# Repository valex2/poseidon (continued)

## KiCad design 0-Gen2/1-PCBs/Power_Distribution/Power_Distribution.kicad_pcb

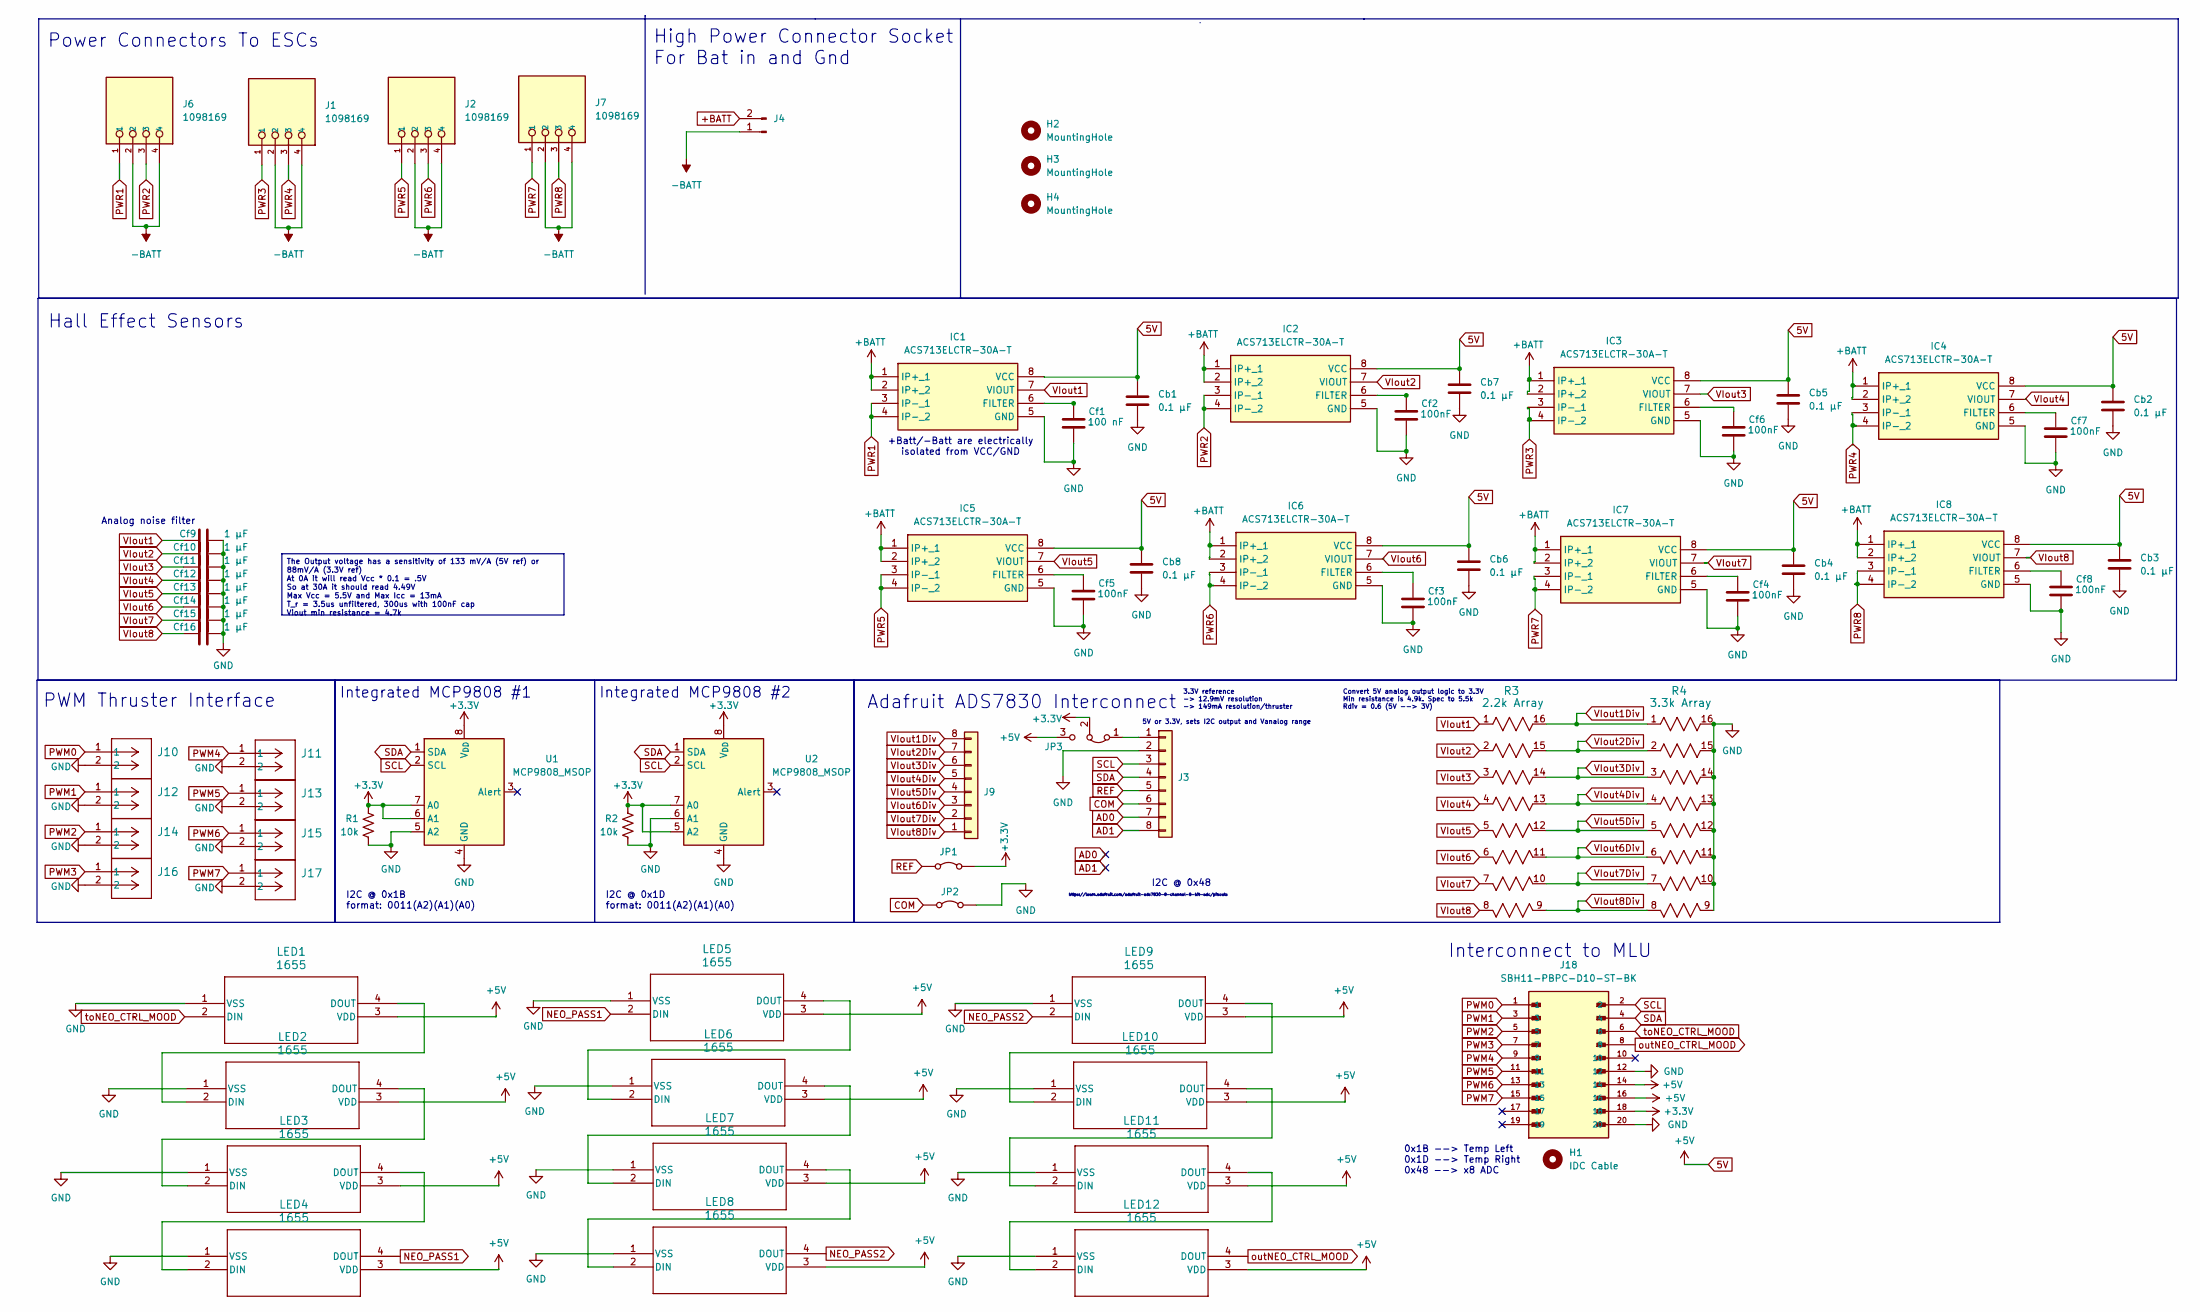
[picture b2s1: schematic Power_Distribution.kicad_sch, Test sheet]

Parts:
Cb1, Cb2, Cb3, Cb4, Cb5, Cb6, Cb7, Cb8: 0.1 µF; C_0805_2012Metric_Pad1.18x1.45mm_HandSolder
Cf1: 100 nF; C_0805_2012Metric_Pad1.18x1.45mm_HandSolder
Cf2, Cf3, Cf4, Cf5, Cf6, Cf7, Cf8: 100nF; C_0805_2012Metric_Pad1.18x1.45mm_HandSolder
Cf9, Cf10, Cf11, Cf12, Cf13, Cf14, Cf15, Cf16: 1 µF; C_0805_2012Metric_Pad1.18x1.45mm_HandSolder
H1: IDC Cable
H2, H3, H4: MountingHole; MountingHole_3.2mm_M3
IC1, IC8: ACS713ELCTR-30A-T; ACS711ELCTR25ABT; Manufacturer_Part_Number ACS713ELCTR-30A-T
IC2, IC3, IC4, IC5, IC6, IC7: ACS713ELCTR-30A-T; MyHalleffectSensor; Manufacturer_Part_Number ACS713ELCTR-30A-T
J1, J2, J6, J7: 1098169; PHOENIX_1098169
J3, J9: Conn_01x08; PinHeader_1x08_P2.54mm_Vertical
J4: Conn_01x02_Pin; AMASS_XT60IPW-M_1x03_P7.20mm_Horizontal
J10, J11, J12, J13, J14, J15, J16, J17: 430450228; CONN_SD-43045-010_02_MOL
J18: SBH11-PBPC-D10-ST-BK; SULLINS_SBH11-PBPC-D10-ST-BK; PARTREV J
JP1, JP2: Jumper_2_Bridged; SolderJumper-2_P1.3mm_Bridged2Bar_RoundedPad1.0x1.5mm
JP3: Jumper_3_Bridged12; SolderJumper-3_P1.3mm_Bridged2Bar12_RoundedPad1.0x1.5mm
LED1, LED2, LED3, LED4, LED5, LED6, LED7, LED8, LED9, LED10, LED11, LED12: 1655; LED_LiteOn_LTST-E563C_PLCC4_5.0x5.0mm_P3.2mm_HandSoldering
R1, R2: 10k; R_0805_2012Metric_Pad1.20x1.40mm_HandSolder
R3: 2.2k Array; 2506_8x_Resistor_Array
R4: 3.3k Array; 2506_8x_Resistor_Array
U1, U2: MCP9808_MSOP; MSOP-8_3x3mm_P0.65mm

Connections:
5V: Cb1.1, Cb2.1, Cb3.1, Cb4.1, Cb5.1, Cb6.1, Cb7.1, Cb8.1, IC1.8 (VCC), IC2.8 (VCC), IC3.8 (VCC), IC4.8 (VCC), IC5.8 (VCC), IC6.8 (VCC), IC7.8 (VCC), IC8.8 (VCC), J18.14, J18.16, JP3.3 (B), LED1.3 (VDD), LED2.3 (VDD), LED3.3 (VDD), LED4.3 (VDD), LED5.3 (VDD), LED6.3 (VDD), LED7.3 (VDD), LED8.3 (VDD), LED9.3 (VDD), LED10.3 (VDD), LED11.3 (VDD), LED12.3 (VDD)
+3.3V: J18.18, JP1.2 (B), JP3.2 (C), R1.1, R2.1, U1.6 (A1), U1.7 (A0), U1.8 (V_{DD}), U2.5 (A2), U2.7 (A0), U2.8 (V_{DD})
+BATT: IC1.1 (IP+_1), IC1.2 (IP+_2), IC2.1 (IP+_1), IC2.2 (IP+_2), IC3.1 (IP+_1), IC3.2 (IP+_2), IC4.1 (IP+_1), IC4.2 (IP+_2), IC5.1 (IP+_1), IC5.2 (IP+_2), IC6.1 (IP+_1), IC6.2 (IP+_2), IC7.1 (IP+_1), IC7.2 (IP+_2), IC8.1 (IP+_1), IC8.2 (IP+_2), J4.2
-BATT: J1.2, J1.4, J2.2, J2.4, J4.1, J6.2, J6.4, J7.2, J7.4
AD0: J3.7
AD1: J3.8
COM: J3.6, JP2.1 (A)
GND: Cb1.2, Cb2.2, Cb3.2, Cb4.2, Cb5.2, Cb6.2, Cb7.2, Cb8.2, Cf1.2, Cf2.2, Cf3.2, Cf4.2, Cf5.2, Cf6.2, Cf7.2, Cf8.2, Cf9.2, Cf10.2, Cf11.2, Cf12.2, Cf13.2, Cf14.2, Cf15.2, Cf16.2, IC1.5 (GND), IC2.5 (GND), IC3.5 (GND), IC4.5 (GND), IC5.5 (GND), IC6.5 (GND), IC7.5 (GND), IC8.5 (GND), J3.2, J10.2, J11.2, J12.2, J13.2, J14.2, J15.2, J16.2, J17.2, J18.12, J18.20, JP2.2 (B), LED1.1 (VSS), LED2.1 (VSS), LED3.1 (VSS), LED4.1 (VSS), LED5.1 (VSS), LED6.1 (VSS), LED7.1 (VSS), LED8.1 (VSS), LED9.1 (VSS), LED10.1 (VSS), LED11.1 (VSS), LED12.1 (VSS), R1.2, R2.2, R4.9, R4.10, R4.11, R4.12, R4.13, R4.14, R4.15, R4.16, U1.4 (GND), U1.5 (A2), U2.4 (GND), U2.6 (A1)
NEO_PASS1: LED4.4 (DOUT), LED5.2 (DIN)
NEO_PASS2: LED8.4 (DOUT), LED9.2 (DIN)
unnamed: Cf1.1, IC1.6 (FILTER)
unnamed: Cf2.1, IC2.6 (FILTER)
unnamed: Cf6.1, IC3.6 (FILTER)
unnamed: Cf7.1, IC4.6 (FILTER)
unnamed: Cf5.1, IC5.6 (FILTER)
unnamed: Cf3.1, IC6.6 (FILTER)
unnamed: Cf4.1, IC7.6 (FILTER)
unnamed: Cf8.1, IC8.6 (FILTER)
unnamed: J3.1, JP3.1 (A)
unnamed: LED1.4 (DOUT), LED2.2 (DIN)
unnamed: LED2.4 (DOUT), LED3.2 (DIN)
unnamed: LED3.4 (DOUT), LED4.2 (DIN)
unnamed: LED5.4 (DOUT), LED6.2 (DIN)
unnamed: LED6.4 (DOUT), LED7.2 (DIN)
unnamed: LED7.4 (DOUT), LED8.2 (DIN)
unnamed: LED9.4 (DOUT), LED10.2 (DIN)
unnamed: LED10.4 (DOUT), LED11.2 (DIN)
unnamed: LED11.4 (DOUT), LED12.2 (DIN)
PWM0: J10.1, J18.1
PWM1: J12.1, J18.3
PWM2: J14.1, J18.5
PWM3: J16.1, J18.7
PWM4: J11.1, J18.9
PWM5: J13.1, J18.11
PWM6: J15.1, J18.13
PWM7: J17.1, J18.15
PWR1: IC1.3 (IP-_1), IC1.4 (IP-_2), J6.1
PWR2: IC2.3 (IP-_1), IC2.4 (IP-_2), J6.3
PWR3: IC3.3 (IP-_1), IC3.4 (IP-_2), J1.1
PWR4: IC4.3 (IP-_1), IC4.4 (IP-_2), J1.3
PWR5: IC5.3 (IP-_1), IC5.4 (IP-_2), J2.1
PWR6: IC6.3 (IP-_1), IC6.4 (IP-_2), J2.3
PWR7: IC7.3 (IP-_1), IC7.4 (IP-_2), J7.1
PWR8: IC8.3 (IP-_1), IC8.4 (IP-_2), J7.3
REF: J3.5, JP1.1 (A)
SCL: J3.3, J18.2, U1.2 (SCL), U2.2 (SCL)
SDA: J3.4, J18.4, U1.1 (SDA), U2.1 (SDA)
VIout1: Cf9.1, IC1.7 (VIOUT), R3.1
VIout1Div: J9.8, R3.16, R4.1
VIout2: Cf10.1, IC2.7 (VIOUT), R3.2
VIout2Div: J9.7, R3.15, R4.2
VIout3: Cf11.1, IC3.7 (VIOUT), R3.3
VIout3Div: J9.6, R3.14, R4.3
VIout4: Cf12.1, IC4.7 (VIOUT), R3.4
VIout4Div: J9.5, R3.13, R4.4
VIout5: Cf13.1, IC5.7 (VIOUT), R3.5
VIout5Div: J9.4, R3.12, R4.5
VIout6: Cf14.1, IC6.7 (VIOUT), R3.6
VIout6Div: J9.3, R3.11, R4.6
VIout7: Cf15.1, IC7.7 (VIOUT), R3.7
VIout7Div: J9.2, R3.10, R4.7
VIout8: Cf16.1, IC8.7 (VIOUT), R3.8
VIout8Div: J9.1, R3.9, R4.8
outNEO_CTRL_MOOD: J18.8, LED12.4 (DOUT)
toNEO_CTRL_MOOD: J18.6, LED1.2 (DIN)

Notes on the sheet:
The Output voltage has a sensitivity of 133 mV/A (5V ref) or 88mV/A (3.3V ref) At 0A it will read Vcc * 0.1 = .5V So at 30A it should read 4.49V Max Vcc = 5.5V and Max Icc = 13mA T_r = 3.5us unfiltered, 300us with 100nF cap Viout min resistance = 4.7k
Interconnect to MLU
Convert 5V analog output logic to 3.3V Min resistance is 4.9k. Spec to 5.5k Rdiv = 0.6 (5V --> 3V)
Analog noise filter
+Batt/-Batt are electrically isolated from VCC/GND
https://learn.adafruit.com/adafruit-ads7830-8-channel-8-bit-adc/pinouts
I2C @ 0x1D format: 0011(A2)(A1)(A0)
I2C @ 0x48
Adafruit ADS7830 Interconnect
5V or 3.3V, sets I2C output and Vanalog range
0x1B --> Temp Left 0x1D --> Temp Right 0x48 --> x8 ADC
High Power Connector Socket For Bat in and Gnd
Integrated MCP9808 #1
Integrated MCP9808 #2
Power Connectors To ESCs
3.3V reference -> 12.9mV resolution -> 149mA resolution/thruster
PWM Thruster Interface
I2C @ 0x1B format: 0011(A2)(A1)(A0)
Hall Effect Sensors

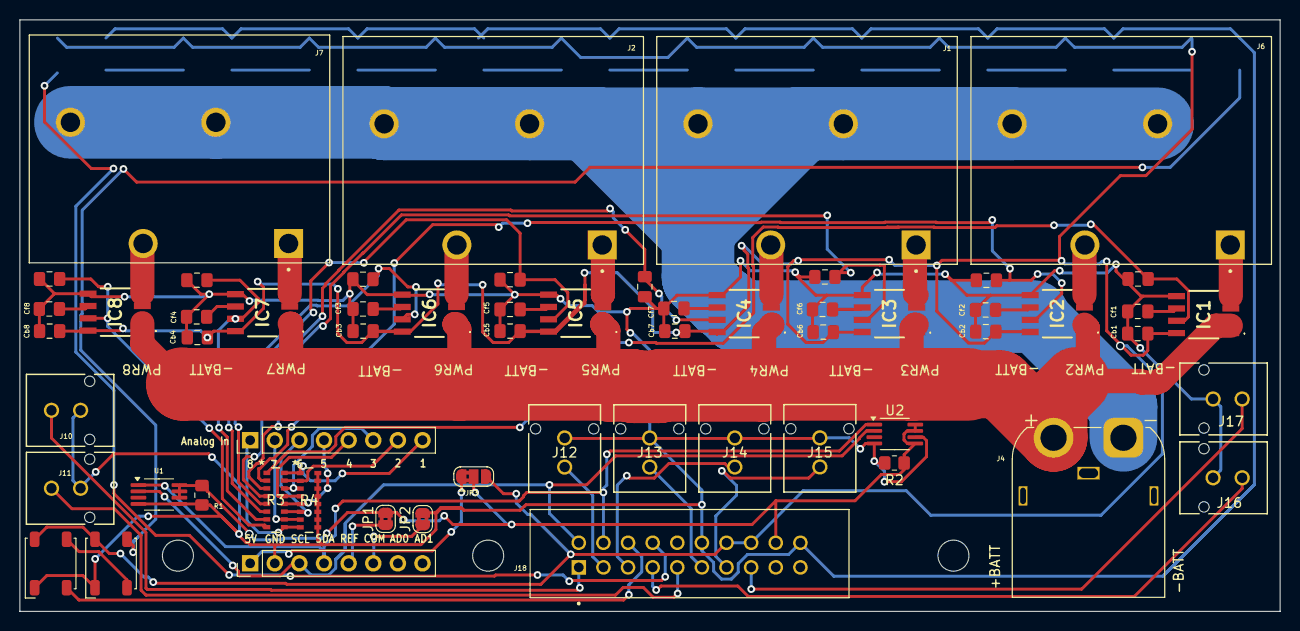
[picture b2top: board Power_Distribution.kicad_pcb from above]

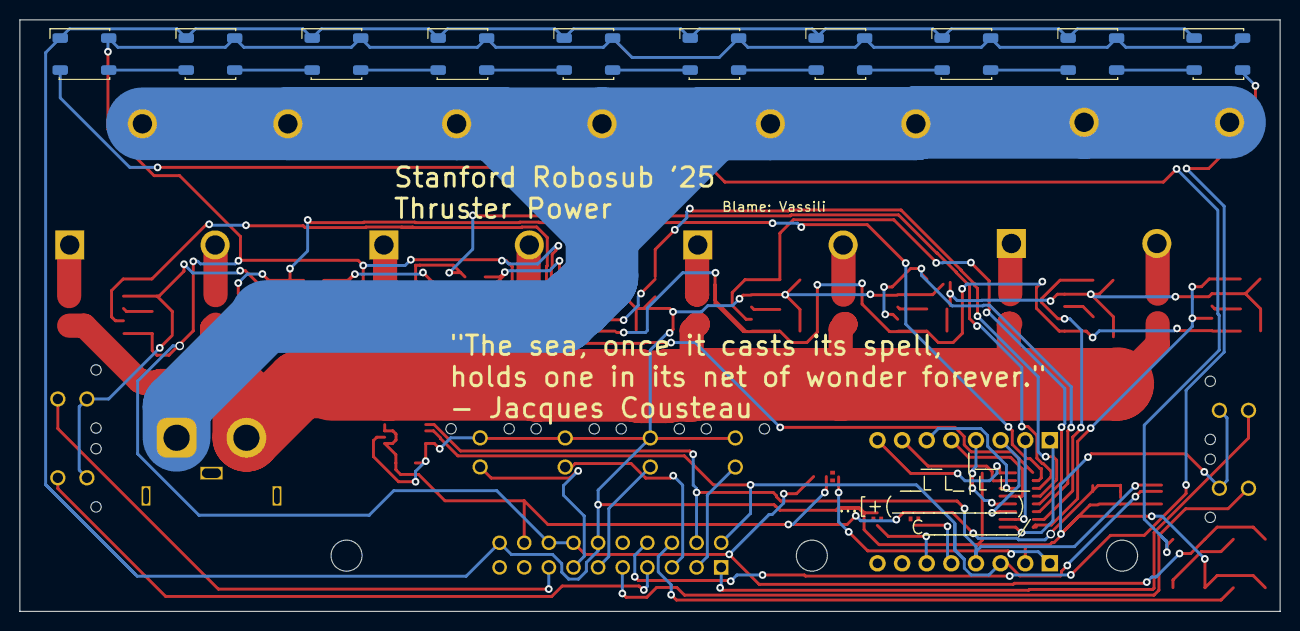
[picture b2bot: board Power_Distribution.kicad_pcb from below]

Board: 2 copper layers, 130.0 x 61.0 mm, 72 parts (10 on the bottom side), 63 nets.

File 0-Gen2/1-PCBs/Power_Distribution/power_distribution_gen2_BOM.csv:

"Reference","Value","Qty","Supplier 1","Supplier 1 S/N"
"Cb1,Cb2,Cb3,Cb4,Cb5,Cb6,Cb7,Cb8,Cf1,Cf2,Cf3,Cf4,Cf5,Cf6,Cf7,Cf8","-- mixed values --","16","https://www.digikey.com/en/products/detail/yageo/CC0805KRX7R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","311-1140-1-ND"
"Cf9,Cf10,Cf11,Cf12,Cf13,Cf14,Cf15,Cf16","1 µF","8","https://www.digikey.com/en/products/detail/samsung-electro-m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","1276-1029-1-ND"
"IC1,IC2,IC3,IC4,IC5,IC6,IC7,IC8","ACS713ELCTR-30A-T","8","https://www.digikey.com/en/products/detail/allegro-microsyst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","620-1193-1-ND"
"J1,J2,J6,J7","1098169","4","https://www.digikey.com/en/products/detail/phoenix-contact/1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","277-1098169-ND"
"J3,J4,J9,JP1,JP2,LED1,LED2,LED3,LED4,LED5,LED6,LED7,LED8,LED9,LED10,LED11,LED12","-- mixed values --","17","",""
"J10,J11,J12,J13,J14,J15,J16,J17","430450228","8","https://www.digikey.com/en/products/detail/molex/0430450228/3310183","WM10659-ND"
"J18","SBH11-PBPC-D10-ST-BK","1","https://www.digikey.com/en/products/detail/sullins-connector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","S9172-ND"
"R1,R2","10k","2","https://www.digikey.com/en/products/detail/panasonic-electro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","P10KACT-ND"
"R3","2.2k Array","1","https://www.digikey.com/en/products/detail/cts-resistor-prod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","60-742C163222JPCT-ND"
"R4","3.3k Array","1","https://www.digikey.com/en/products/detail/cts-resistor-prod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","60-742C163332JPCT-ND"
"U1,U2","MCP9808_MSOP","2","https://www.digikey.com/en/products/detail/microchip-technol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","MCP9808T-E/MSCT-ND"

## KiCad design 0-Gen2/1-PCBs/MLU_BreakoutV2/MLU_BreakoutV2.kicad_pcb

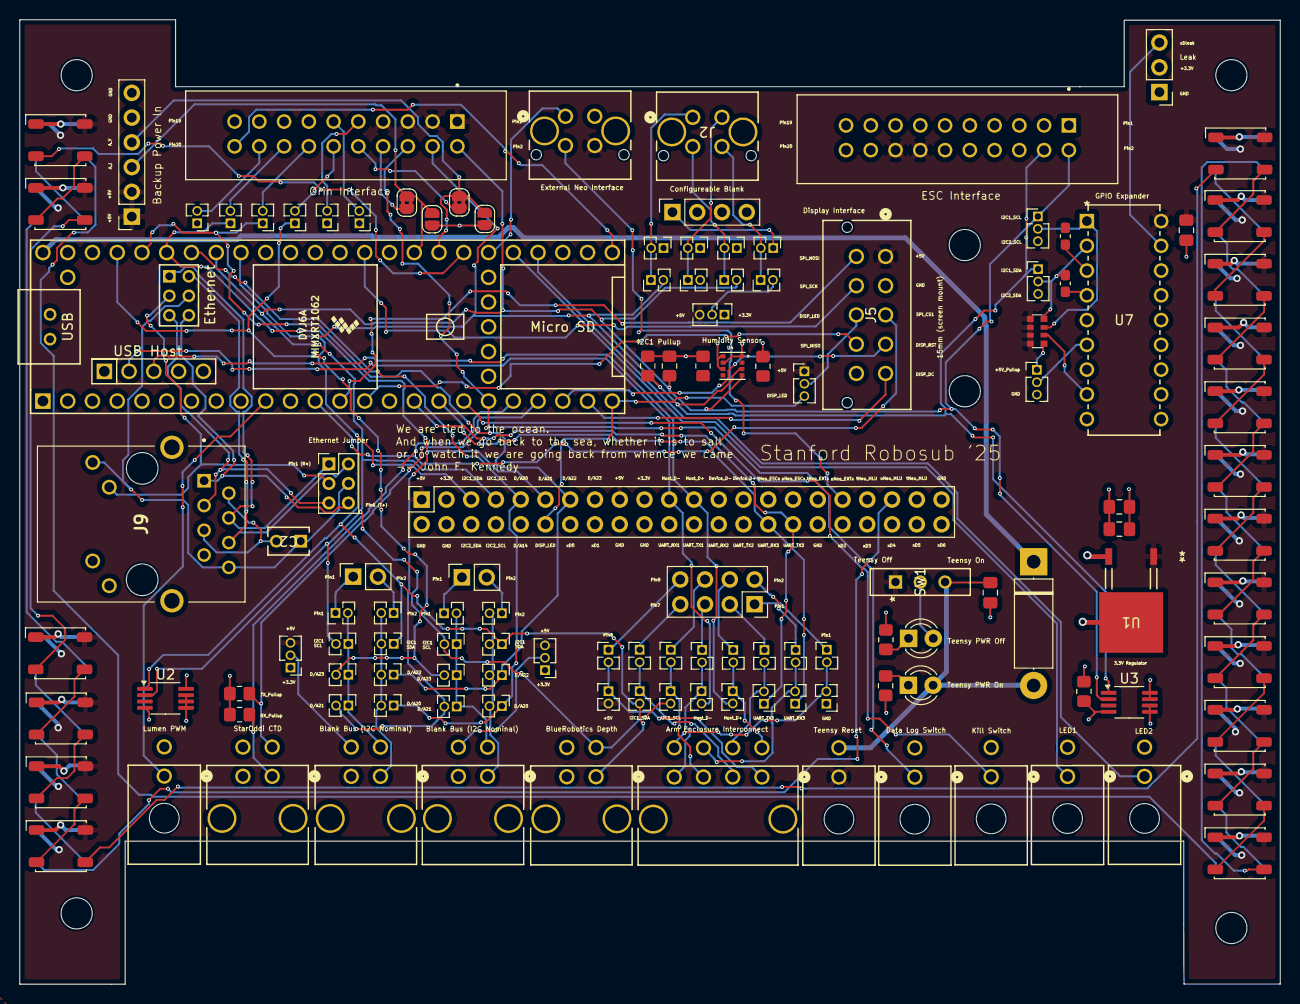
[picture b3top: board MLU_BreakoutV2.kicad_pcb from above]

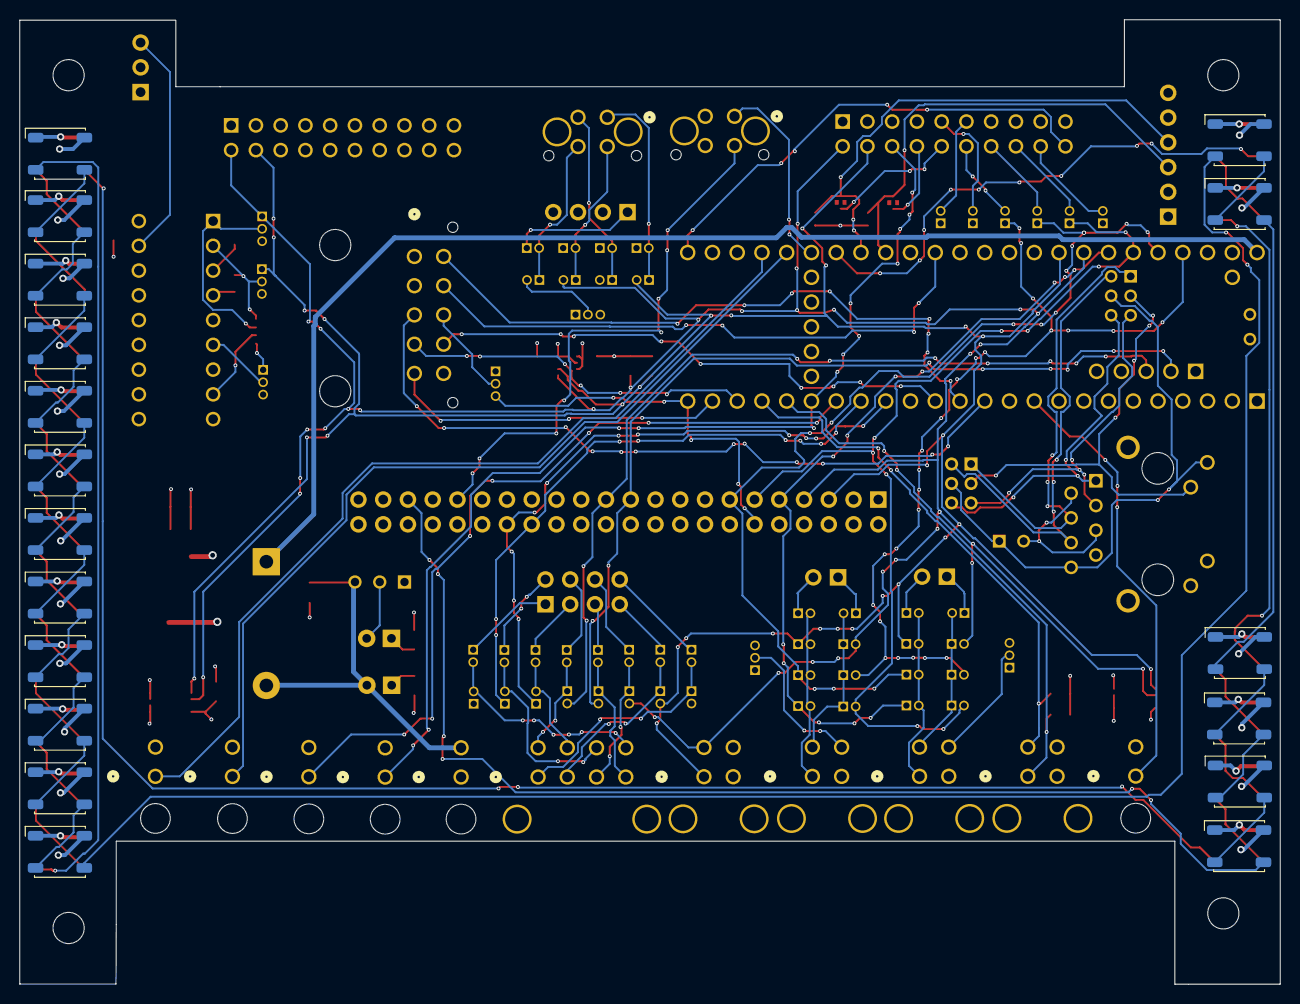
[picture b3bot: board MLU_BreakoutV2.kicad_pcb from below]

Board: 4 copper layers, 129.3 x 99.0 mm, 151 parts (18 on the bottom side), 157 nets.

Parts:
C1, C3, C6: 10uF; C_0805_2012Metric_Pad1.18x1.45mm_HandSolder
C2: 0.1uF; K104K15X7RF5TL2_VIS
C4, C5: 135p; C_0603_1608Metric_Pad1.08x0.95mm_HandSolder
C7: 1uF; C_0805_2012Metric_Pad1.18x1.45mm_HandSolder
D1: 1N5817; D_5W_P12.70mm_Horizontal
D2, D3: LED; LED_D3.0mm
H1, H3, H4, H12: MountingHole; MountingHole_3.2mm_M3
H8, H9: MountingHole_3.2mm_M3
J2, J4: 430450422; CONN_SD-43045-009_04_MOL
J3: Conn_01x03_Pin; PinHeader_1x03_P2.54mm_Vertical
J5: 430451027; CONN_SD-43045-010_10_MOL
J6, J20, J21, J22, J23, J25: 430450228; CONN_SD-43045-001_02_MOL
J7, J13: SBH11-PBPC-D10-ST-BK; SULLINS_SBH11-PBPC-D10-ST-BK
J8: Conn_02x22_Odd_Even; PinSocket_2x22_P2.54mm_Vertical
J9: J1B1211CCD
J10: Conn_02x03_Odd_Even; PinHeader_2x03_P2.00mm_Vertical
J11, J17, J18, J19: 430450422; CONN_SD-43045-008_04_MOL
J12: PixHawk PM02; PinSocket_1x06_P2.54mm_Vertical
J14, J31: Conn_01x02_Socket; PinSocket_1x02_P2.54mm_Vertical
J26: 430450821; CONN_SD-43045-008_08_MOL
J27: PinSocket_2x04_P2.54mm_Vertical
J28: Conn_01x04_Socket; PinSocket_1x04_P2.54mm_Vertical
JP2, JP8, JP9, JP10, JP17, JP40, JP58: Jumper_3_Bridged12; PinHeader_1x03_P1.27mm_Vertical
JP3, JP11, JP12, JP13, JP14, JP15, JP16, JP18, JP19, JP20, JP21, JP22, JP23, JP24, JP25, JP26, JP27, JP28, JP29, JP30, JP31, JP41, JP42, JP43, JP44, JP49, JP50, JP51, JP52, JP53, JP57, JP59, JP60, JP67: Jumper_2_Small_Open; PinHeader_1x02_P1.27mm_Vertical
JP4, JP7: Jumper_2_Small_Open; SolderJumper-2_P1.3mm_Open_RoundedPad1.0x1.5mm
JP5, JP6: Jumper_2_Small_Bridged; SolderJumper-2_P1.3mm_Bridged2Bar_RoundedPad1.0x1.5mm
JP32, JP33, JP34, JP35, JP36, JP37, JP38, JP39, JP45, JP46, JP47, JP48: Jumper_2_Small_Bridged; PinHeader_1x02_P1.27mm_Vertical
LED1, LED2, LED3, LED4, LED5, LED6, LED7, LED8, LED9, LED10, LED11, LED12, LED13, LED14, LED15, LED16, LED17, LED18, LED19, LED20, LED21, LED22, LED23, LED24, LED25, LED26, LED27, LED28, LED29, LED30, LED31, LED32, LED33, LED34, LED35, LED36: 1655; LED_LiteOn_LTST-E563C_PLCC4_5.0x5.0mm_P3.2mm_HandSoldering
R1, R2, R3, R4, R5, R8, R9: 10k; R_0805_2012Metric_Pad1.20x1.40mm_HandSolder
R6, R7: 140; R_0805_2012Metric_Pad1.20x1.40mm_HandSolder
RN1: 10kΩ; R_Array_Convex_4x0612
SW1: 09.03201.02; 09.03201_EAO
U1: BA033CC0FP-E2; TO252-3_ROM
U2, U3: MCP9808_MSOP; MSOP-8_3x3mm_P0.65mm
U4: BME280
U6: Teensy4.1; Teensy41
U7: MCP23008-E_P; MCP3008

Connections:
+3.3V: C6.1, C7.1, J3.2, J7.18, J8.3, J8.19, J17.4, J18.4, J21.2, J25.2, JP2.1 (A), JP17.1 (A), JP58.1 (A), R1.1, R2.1, R3.1, R4.1, R5.1, R8.2, R9.2, U1.3 (OUT), U2.8 (V_{DD}), U3.7 (A0), U3.8 (V_{DD}), U4.6 (VDDIO), U4.8 (VDD)
+5V: C3.1, J4.4, J5.1, J6.1, J7.14, J7.16, J8.1, J8.17, J12.1, J12.2, J13.1, J13.3, J13.5, J13.7, JP2.3 (B), JP17.3 (B), JP34.2 (B), JP40.1 (A), JP58.3 (B), LED1.3 (VDD), LED2.3 (VDD), LED3.3 (VDD), LED4.3 (VDD), LED5.3 (VDD), LED6.3 (VDD), LED7.3 (VDD), LED8.3 (VDD), LED9.3 (VDD), LED10.3 (VDD), LED11.3 (VDD), LED12.3 (VDD), LED13.3 (VDD), LED14.3 (VDD), LED15.3 (VDD), LED16.3 (VDD), LED17.3 (VDD), LED18.3 (VDD), LED19.3 (VDD), LED20.3 (VDD), LED21.3 (VDD), LED22.3 (VDD), LED23.3 (VDD), LED24.3 (VDD), LED25.3 (VDD), LED26.3 (VDD), LED27.3 (VDD), LED28.3 (VDD), LED29.3 (VDD), LED30.3 (VDD), LED31.3 (VDD), LED32.3 (VDD), LED33.3 (VDD), LED34.3 (VDD), LED35.3 (VDD), LED36.3 (VDD), RN1.5 (R4.2), RN1.6 (R3.2), RN1.7 (R2.2), RN1.8 (R1.2), SW1.1, U1.1 (Vcc), U7.18 (VDD)
Analog_Current: J12.3, JP4.1 (A), JP5.2 (B), U6.33 (41_A17)
Analog_Voltage: J12.4, JP6.2 (B), JP7.2 (B), U6.32 (40_A16)
DISP_DC: J5.5, U6.23 (31_CTX3)
DISP_LED: J8.12, JP40.3 (B), U6.24 (32_OUT1B)
DISP_RST: J5.4, U6.22 (30_CRX3)
Device_D+: J8.27, JP41.1 (A), U6.67 (D+)
Device_D-: J8.25, JP49.1 (A), U6.66 (D-)
Dled1: J22.1, U6.29 (37_CS)
Dled2: J23.1, U6.28 (36_CS)
Dswitch1: J21.1, U6.18 (26_A12_MOSI1)
Dswitch2: J13.6, J25.1, U6.19 (27_A13_SCK1)
D/A14: J8.10, U6.36 (14_A0_TX3_SPDIF_OUT)
D/A20: J8.9, JP16.1 (A), JP19.1 (A), JP53.1 (A), U6.42 (20_A6_TX5_LRCLK1)
D/A21: J8.11, JP24.2 (B), JP52.1 (A), JP60.2 (B), U6.43 (21_A7_RX5_BCLK1)
D/A22: J8.13, JP15.1 (A), JP20.1 (A), JP51.1 (A), U6.44 (22_A8_CTX1)
D/A23: J8.15, JP50.1 (A), JP57.2 (B), JP59.2 (B), U6.45 (23_A9_CRX1_MCLK1)
ETH_GND: C2.1, J9.8 (GND), J9.9, J10.4, U6.64 (GND)
GND: C1.2, C3.2, C4.2, C5.2, C6.2, C7.2, J3.1, J4.2, J5.2, J7.12, J7.20, J8.2, J8.4, J8.18, J8.20, J8.34, J8.43, J11.2, J12.5, J12.6, J13.13, J13.15, J13.17, J13.19, J17.2, J18.2, J19.2, J20.2, J22.2, J23.2, JP4.2 (B), JP7.1 (A), JP10.3 (B), JP38.1 (A), JP46.2 (B), LED1.1 (VSS), LED2.1 (VSS), LED3.1 (VSS), LED4.1 (VSS), LED5.1 (VSS), LED6.1 (VSS), LED7.1 (VSS), LED8.1 (VSS), LED9.1 (VSS), LED10.1 (VSS), LED11.1 (VSS), LED12.1 (VSS), LED13.1 (VSS), LED14.1 (VSS), LED15.1 (VSS), LED16.1 (VSS), LED17.1 (VSS), LED18.1 (VSS), LED19.1 (VSS), LED20.1 (VSS), LED21.1 (VSS), LED22.1 (VSS), LED23.1 (VSS), LED24.1 (VSS), LED25.1 (VSS), LED26.1 (VSS), LED27.1 (VSS), LED28.1 (VSS), LED29.1 (VSS), LED30.1 (VSS), LED31.1 (VSS), LED32.1 (VSS), LED33.1 (VSS), LED34.1 (VSS), LED35.1 (VSS), LED36.1 (VSS), R3.2, R6.2, R7.2, U1.2 (GND), U2.4 (GND), U2.5 (A2), U2.6 (A1), U2.7 (A0), U3.4 (GND), U3.5 (A2), U3.6 (A1), U4.1 (GND), U4.7 (GND), U6.1 (GND), U6.34 (GND), U6.47 (GND), U7.3 (A2), U7.4 (A1), U7.5 (A0), U7.9 (VSS)
GPIOExp_INT: RN1.2 (R2.1), U6.37 (15_A1_RX3_SPDIF_IN), U7.8 (INT)
Host_D+: J8.23, JP39.2 (B), U6.57 (D+)
Host_D-: J8.21, JP37.2 (B), U6.56 (D-)
I2C1_SCL: J7.2, J8.7, J13.2, J17.3, JP8.1 (A), JP11.2 (B), JP23.2 (B), JP36.2 (B), JP47.2 (B), R5.2, U2.2 (SCL), U3.2 (SCL), U4.4 (SCK), U6.41 (19_A5_SCL)
I2C1_SDA: J7.4, J8.5, J13.4, J17.1, JP9.1 (A), JP14.1 (A), JP18.1 (A), JP35.2 (B), JP45.2 (B), R4.2, U2.1 (SDA), U3.1 (SDA), U4.3 (SDI), U6.40 (18_A4_SDA)
I2C2_SCL: J8.8, JP8.3 (B), U6.38 (16_A2_RX4_SCL1)
I2C2_SDA: J8.6, JP9.3 (B), U6.39 (17_A3_TX4_SDA1)
LED: J9.10, J10.3, U6.61 (LED)
Lumen_PWM: J20.1, U6.10 (8_TX2_IN1)
NEO_PASS1: LED4.4 (DOUT), LED5.2 (DIN)
NEO_PASS2: LED8.4 (DOUT), LED9.2 (DIN)
NEO_PASS3: LED12.4 (DOUT), LED13.2 (DIN)
NEO_PASS4: LED16.4 (DOUT), LED17.2 (DIN)
NEO_PASS5: LED20.4 (DOUT), LED21.2 (DIN)
NEO_PASS6: LED24.4 (DOUT), LED25.2 (DIN)
NEO_PASS7: LED28.4 (DOUT), LED29.2 (DIN)
NEO_PASS8: LED32.4 (DOUT), LED33.2 (DIN)
unnamed: C2.2, J9.2, J9.5
unnamed: C1.1, D1.2 (A), D3.2 (A), J6.2, SW1.3
unnamed: D2.2 (A), SW1.2
unnamed: D2.1 (K), R6.1
unnamed: D3.1 (K), R7.1
unnamed: J14.1, JP22.1 (A)
unnamed: J14.2, JP21.1 (A)
unnamed: J27.1, JP31.1 (A)
unnamed: J27.2, JP30.1 (A)
unnamed: J27.3, JP29.1 (A)
unnamed: J27.4, JP28.1 (A)
unnamed: J27.5, JP27.1 (A)
unnamed: J27.6, JP26.1 (A)
unnamed: J27.7, JP25.1 (A)
unnamed: J27.8, JP3.1 (A)
unnamed: J28.1, JP44.1 (A)
unnamed: J28.2, JP43.1 (A)
unnamed: J28.3, JP42.1 (A)
unnamed: J28.4, JP67.1 (A)
unnamed: J31.1, JP12.1 (A)
unnamed: J31.2, JP13.1 (A)
unnamed: JP2.2 (C), JP48.2 (B)
unnamed: J26.1, JP3.2 (B), JP34.1 (A)
unnamed: J13.8, JP5.1 (A)
unnamed: J13.10, JP6.1 (A)
unnamed: C4.1, JP8.2 (C), RN1.3 (R3.1), U7.1 (SCL)
unnamed: C5.1, JP9.2 (C), RN1.4 (R4.1), U7.2 (SDA)
unnamed: JP10.1 (A), RN1.1 (R1.1)
unnamed: JP10.2 (C), U7.6 (*RESET)
unnamed: J19.3, JP11.1 (A), JP12.2 (B), JP59.1 (A), JP60.1 (A)
unnamed: J19.1, JP13.2 (B), JP14.2 (B), JP15.2 (B), JP16.2 (B)
unnamed: J19.4, JP17.2 (C)
unnamed: J11.1, JP18.2 (B), JP19.2 (B), JP20.2 (B), JP21.2 (B)
unnamed: J11.3, JP22.2 (B), JP23.1 (A), JP24.1 (A), JP57.1 (A)
unnamed: J26.2, JP25.2 (B), JP35.1 (A)
unnamed: J26.3, JP26.2 (B), JP36.1 (A)
unnamed: J26.4, JP27.2 (B), JP37.1 (A)
unnamed: J26.5, JP28.2 (B), JP39.1 (A)
unnamed: J26.6, JP29.2 (B), JP33.2 (B)
unnamed: J26.7, JP30.2 (B), JP32.2 (B)
unnamed: J26.8, JP31.2 (B), JP38.2 (B)
unnamed: J5.8, JP40.2 (C)
unnamed: J13.11, JP41.2 (B)
unnamed: J2.2, JP42.2 (B), JP46.1 (A)
unnamed: J2.3, JP43.2 (B), JP47.1 (A)
unnamed: J2.4, JP44.2 (B), JP48.1 (A)
unnamed: J2.1, JP45.1 (A), JP67.2 (B)
unnamed: J13.9, JP49.2 (B)
unnamed: J13.12, JP50.2 (B)
unnamed: J13.14, JP51.2 (B)
unnamed: J13.16, JP52.2 (B)
unnamed: J13.18, JP53.2 (B)
unnamed: J11.4, JP58.2 (C)
unnamed: LED1.4 (DOUT), LED2.2 (DIN)
unnamed: LED2.4 (DOUT), LED3.2 (DIN)
unnamed: LED3.4 (DOUT), LED4.2 (DIN)
unnamed: LED5.4 (DOUT), LED6.2 (DIN)
unnamed: LED6.4 (DOUT), LED7.2 (DIN)
unnamed: LED7.4 (DOUT), LED8.2 (DIN)
unnamed: LED9.4 (DOUT), LED10.2 (DIN)
unnamed: LED10.4 (DOUT), LED11.2 (DIN)
unnamed: LED11.4 (DOUT), LED12.2 (DIN)
unnamed: LED13.4 (DOUT), LED14.2 (DIN)
unnamed: LED14.4 (DOUT), LED15.2 (DIN)
unnamed: LED15.4 (DOUT), LED16.2 (DIN)
unnamed: LED17.4 (DOUT), LED18.2 (DIN)
unnamed: LED18.4 (DOUT), LED19.2 (DIN)
unnamed: LED19.4 (DOUT), LED20.2 (DIN)
unnamed: LED21.4 (DOUT), LED22.2 (DIN)
unnamed: LED22.4 (DOUT), LED23.2 (DIN)
unnamed: LED23.4 (DOUT), LED24.2 (DIN)
unnamed: LED25.4 (DOUT), LED26.2 (DIN)
unnamed: LED26.4 (DOUT), LED27.2 (DIN)
unnamed: LED27.4 (DOUT), LED28.2 (DIN)
unnamed: LED29.4 (DOUT), LED30.2 (DIN)
unnamed: LED30.4 (DOUT), LED31.2 (DIN)
unnamed: LED31.4 (DOUT), LED32.2 (DIN)
unnamed: LED33.4 (DOUT), LED34.2 (DIN)
unnamed: LED34.4 (DOUT), LED35.2 (DIN)
unnamed: LED35.4 (DOUT), LED36.2 (DIN)
unnamed: R2.2, U4.2 (CSB)
unnamed: R1.2, U4.5 (SDO)
PWM0: J7.1, U6.2 (0_RX1_CRX2_CS1)
PWM1: J7.3, U6.3 (1_TX1_CTX2_MISO1)
PWM2: J7.5, U6.4 (2_OUT2)
PWM3: J7.7, U6.5 (3_LRCLK2)
PWM4: J7.9, U6.6 (4_BCLK2)
PWM5: J7.11, U6.7 (5_IN2)
PWM6: J7.13, U6.8 (6_OUT1D)
PWM7: J7.15, U6.9 (7_RX2_OUT1A)
R+: J9.4, J10.1, U6.60 (R+)
R-: J9.6, J10.2, U6.65 (R-)
SPI_CS1: J5.3, U6.12 (10_CS_MQSR)
SPI_MISO: J5.9, U6.14 (12_MISO_MQSL)
SPI_MOSI: J5.6, U6.13 (11_MOSI_CTX1)
SPI_SCK: J5.7, U6.35 (13_SCK_LED)
T+: J9.1, J10.6, U6.63 (T+)
T-: J9.3, J10.5, U6.62 (T-)
Teensy_5V: D1.1 (K), U6.48 (VIN)
UART_RX1: J8.24, U6.26 (34_RX8)
UART_RX2: J8.26, J18.1, R9.1, U6.20 (28_RX7)
UART_RX3: J8.30, JP32.1 (A), U6.17 (25_A11_RX6_SDA2)
UART_TX1: J8.22, U6.27 (35_TX8)
UART_TX2: J8.28, J18.3, R8.1, U6.21 (29_TX7)
UART_TX3: J8.32, JP33.1 (A), U6.16 (24_A10_TX6_SCL2)
outNEO_CTRL_ESCs: J7.8, J8.31
outNEO_CTRL_EXTs: J4.3, J8.35
outNEO_CTRL_MLU: J8.39, LED36.4 (DOUT)
toNEO_CTRL_ESCs: J7.6, J8.29, U6.11 (9_OUT1C)
toNEO_CTRL_EXTs: J4.1, J8.33, U6.30 (38_CS1_IN1)
toNEO_CTRL_MLU: J8.37, LED1.2 (DIN), U6.31 (39_MISO1_OUT1A)
toNEO_CTRL_Orin: J8.41, J13.20, U6.25 (33_MCLK2)
xD0: J8.14, U7.10 (GP0)
xD1: J8.16, U7.11 (GP1)
xD2: J8.36, U7.12 (GP2)
xD3: J8.38, U7.13 (GP3)
xD4: J8.40, U7.14 (GP4)
xD5: J8.42, U7.15 (GP5)
xD6: J8.44, U7.16 (GP6)
xDleak: J3.3, U7.17 (GP7)

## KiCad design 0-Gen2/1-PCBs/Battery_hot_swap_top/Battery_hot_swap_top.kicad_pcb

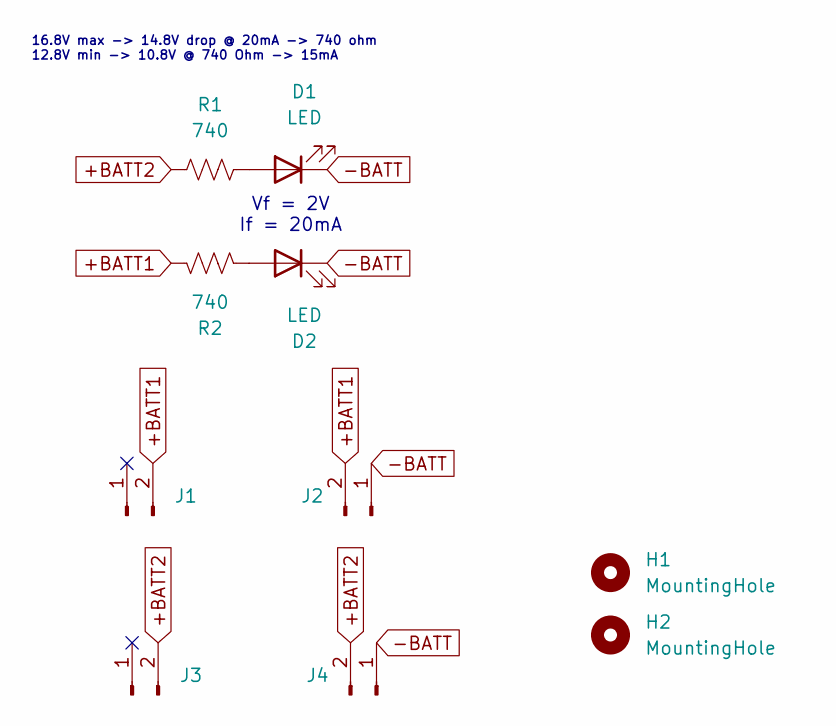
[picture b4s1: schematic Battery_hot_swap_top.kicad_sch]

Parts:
D1, D2: LED; LED_D4.0mm
H1, H2: MountingHole; MountingHole_3.2mm_M3
J1, J3: Conn_01x02_Pin; AMASS_XT60-M_1x02_P7.20mm_Vertical
J2, J4: Conn_01x02_Pin; AMASS_XT60-F_1x02_P7.20mm_Vertical
R1, R2: 740; R_0805_2012Metric_Pad1.20x1.40mm_HandSolder

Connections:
+BATT1: J1.2, J2.2, R2.1
+BATT2: J3.2, J4.2, R1.1
-BATT: D1.1 (K), D2.1 (K), J2.1, J4.1
unnamed: D1.2 (A), R1.2
unnamed: D2.2 (A), R2.2

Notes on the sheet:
16.8V max -> 14.8V drop @ 20mA -> 740 ohm 12.8V min -> 10.8V @ 740 Ohm -> 15mA
Vf = 2V If = 20mA

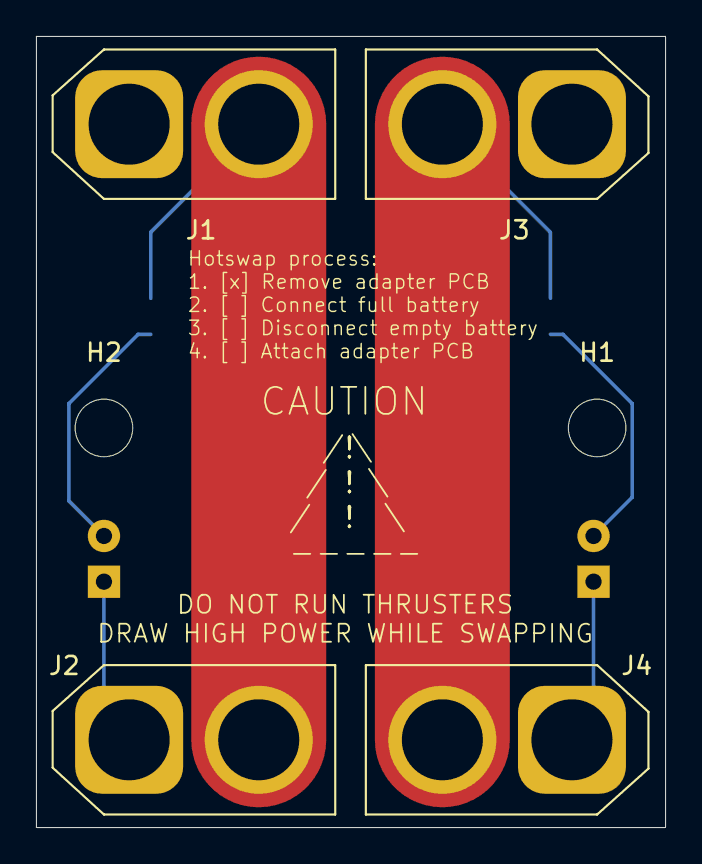
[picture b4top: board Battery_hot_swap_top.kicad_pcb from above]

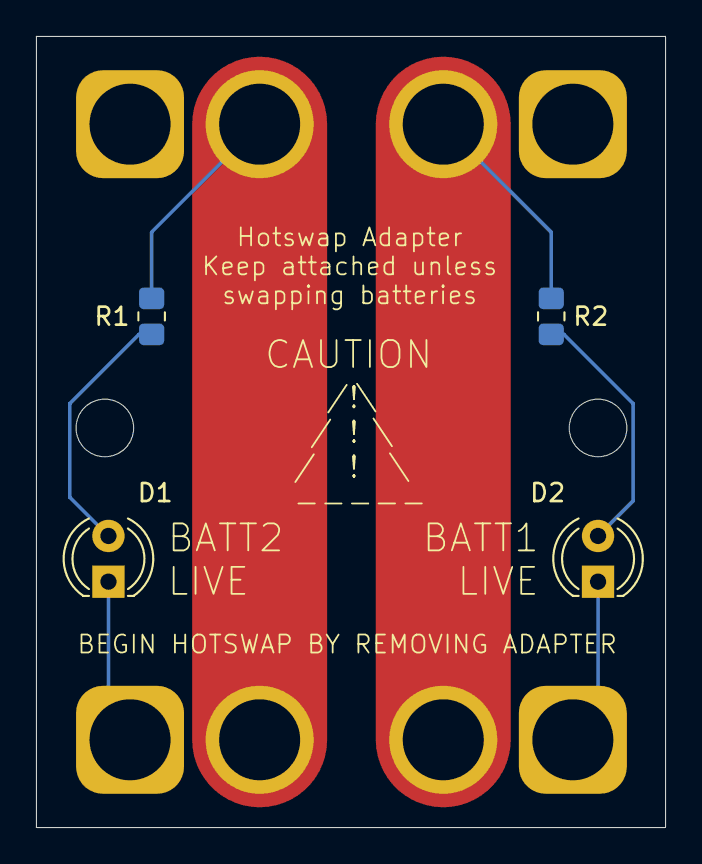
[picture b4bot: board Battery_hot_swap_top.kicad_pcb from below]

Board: 2 copper layers, 34.9 x 43.9 mm, 10 parts (4 on the bottom side), 5 nets.

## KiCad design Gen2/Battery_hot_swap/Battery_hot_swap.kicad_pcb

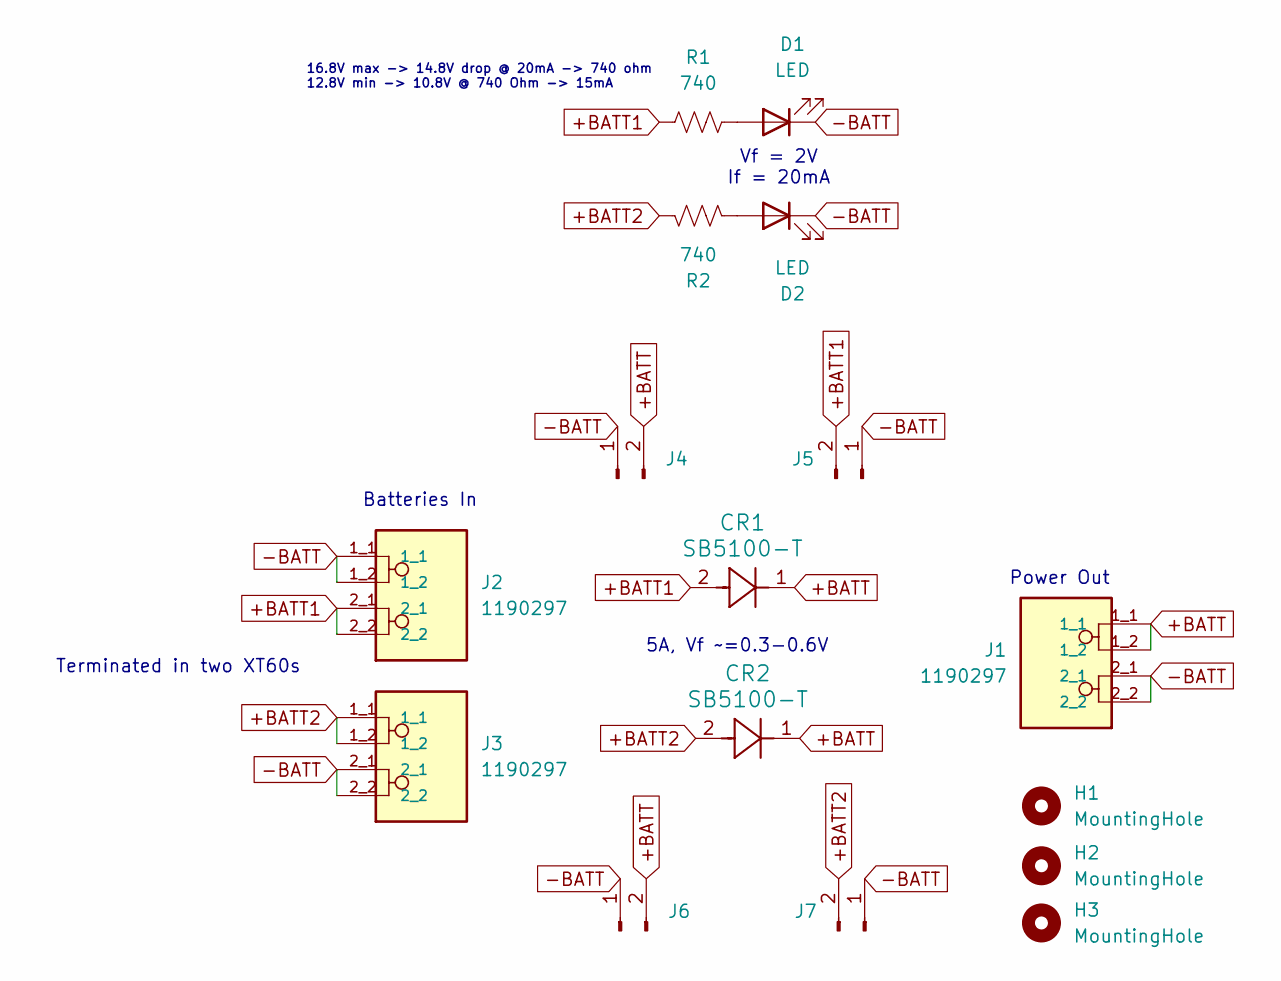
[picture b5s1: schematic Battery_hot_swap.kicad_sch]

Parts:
CR1, CR2: SB5100-T; DO-201AD_DIO
D1, D2: LED; LED_D4.0mm
H1, H2, H3: MountingHole; MountingHole_3.2mm_M3
J1, J2, J3: 1190297; PHOENIX_1190297; PARTREV 03.11.2020
J4, J6: Conn_01x02_Pin; AMASS_XT60-M_1x02_P7.20mm_Vertical
J5, J7: Conn_01x02_Pin; AMASS_XT60-F_1x02_P7.20mm_Vertical
R1, R2: 740; R_0805_2012Metric_Pad1.20x1.40mm_HandSolder

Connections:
+BATT: CR1.1, CR2.1, J1.1_1, J1.1_2, J4.2, J6.2
+BATT1: CR1.2, J2.2_1, J2.2_2, J5.2, R1.1
+BATT2: CR2.2, J3.1_1, J3.1_2, J7.2, R2.1
-BATT: D1.1 (K), D2.1 (K), J1.2_1, J1.2_2, J2.1_1, J2.1_2, J3.2_1, J3.2_2, J4.1, J5.1, J6.1, J7.1
unnamed: D1.2 (A), R1.2
unnamed: D2.2 (A), R2.2

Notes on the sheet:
16.8V max -> 14.8V drop @ 20mA -> 740 ohm 12.8V min -> 10.8V @ 740 Ohm -> 15mA
Batteries In
Power Out
Terminated in two XT60s
Vf = 2V If = 20mA
5A, Vf ~=0.3-0.6V

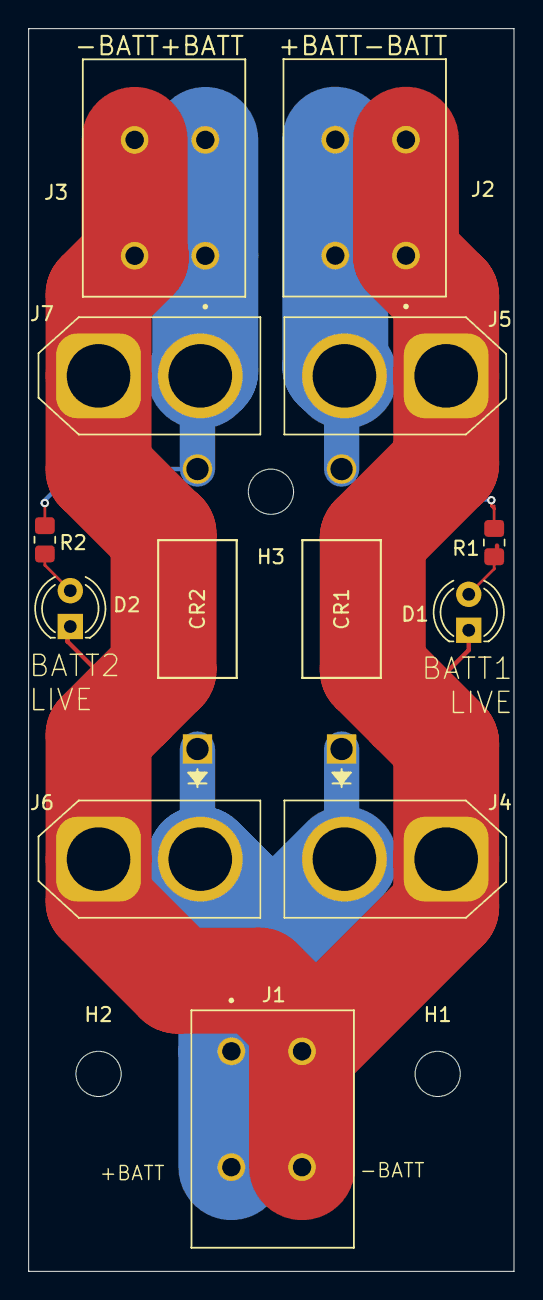
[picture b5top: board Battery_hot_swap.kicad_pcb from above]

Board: 2 copper layers, 34.3 x 87.9 mm, 16 parts (0 on the bottom side), 6 nets.
